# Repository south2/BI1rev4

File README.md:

BI1rev4
=======

BI1 revision 4 (myf14 evaluated, myf17 is work in progress)

The “body interactor”(BI) is a printed circuit board (PCB) with a vibrator motor, an accelerometer, a LiPo battery and battery charger and wireless radio frequency (RF) communication. The board can be programmed with the Arduino software.

The BI is designed for building a wearable autonomous device: With the accelerometer, movement data can be recorded and send to other BI by wireless RF communication. Gestures can be recognised and used for controlling the vibrator motor as well as other devices and applications using wireless communication (e.g. other BIs, computer games).

Different vibration pattern can be used to give the wearer information or feedback. Other use cases for vibration are massage application or moving objects (e.g. “vibrobot”).

The development board is particular suitable for people who are interested in application development using this kind of hardware arrangement and to construct an individual printed encasement for the board. Board, 3D printed encasement and Arduino program together are the individual final product. In addition the wireless communication function offers applications comprising multiple BI in different cases and with different tasks. In contrast changes, adaption or extensions (shields) of the board are rather complex.

www.bodyinteraction.com/about

Encasements

http://www.thingiverse.com/thing:109167

http://www.thingiverse.com/thing:259780

Data

- Atmel Attiny84 (8kbyte)
- LiPo charger (via USB)
- LiPo battery
- vibration motor (PWM controlled)
- BMA020 accelerometer
- two additional I/O ports  
- ISP interface (2×3 pole header) for programming
- RFM12B (915 or 868 Mhz)
- approx.  22×35 mm
- open source hardware

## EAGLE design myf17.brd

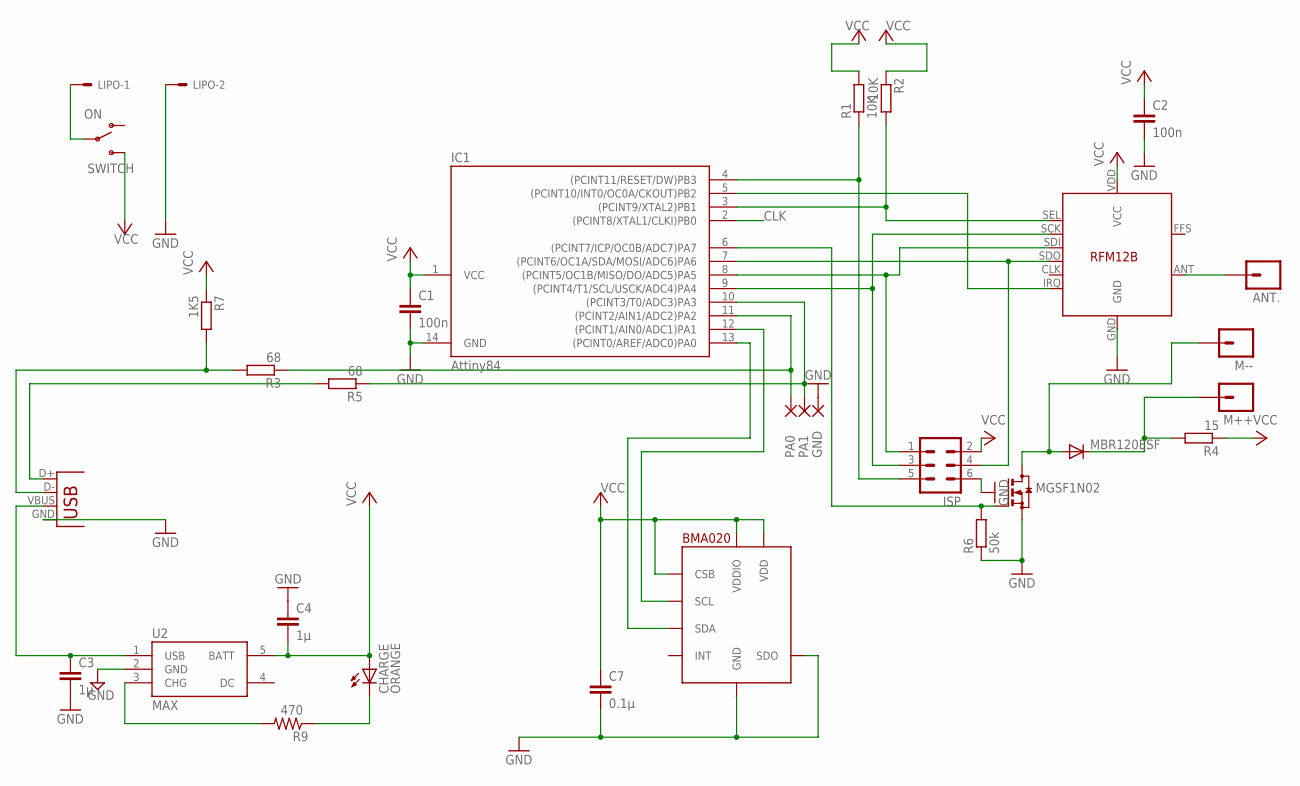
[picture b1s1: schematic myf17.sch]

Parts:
ANT.: M01PTH; 1X01
BMA020: BMA020; LBA-12
C1, C2: 100n; C0603K
C3, C4: 1µ; 0603-CAP
C7: 0.1µ; 0603-CAP
CHARGE: ORANGE; LED-0603
GND: SMD2; SMD1,27-2,54
IC1: Attiny84; SOIC14
ISP: MA03-2S; MA03-2-0.8
LIPO: SM02B-SRSS-TB
M++: M01PTH; 1X01
M--: M01PTH; 1X01
MBR120ESF: CGRM4001-G; SOD-123_MINI-SMA
MGSF1N02: BSS123; SOT23
PA0, PA1: SMD2; SMD1,27-2,54
R1, R2: 10K; R0603
R3, R5: 68; R0603
R4: 15; R0603
R6: 50k; R0603
R7: 1K5; R0603
R9: 470; R0603
RFM12B: RFM12B
SWITCH: ON; SWITCH-SPDT-SMD
U2: MAX; SOT23-5
USB: USB-MICROB

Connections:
CLK: IC1.2 ((PCINT8/XTAL1/CLKI)PB0)
GND: BMA020.P$3 (GND), BMA020.P$7 (SDO), C1.2, C2.2, C3.2, C4.1, C7.2, GND.1, IC1.14 (GND), ISP.6, LIPO.2, MGSF1N02.2 (S), R6.1, RFM12B.GND, U2.2 (GND), USB.GND
LED: BMA020.P$8 (SDA), IC1.13 ((PCINT0/AREF/ADC0)PA0)
unnamed: IC1.4 ((PCINT11/RESET/DW)PB3), ISP.5, R1.1
unnamed: IC1.3 ((PCINT9/XTAL2)PB1), R2.2, RFM12B.SEL
unnamed: ANT..1, RFM12B.ANT
unnamed: IC1.9 ((PCINT4/T1/SCL/USCK/ADC4)PA4), ISP.3, RFM12B.SCK
unnamed: IC1.8 ((PCINT5/OC1B/MISO/DO/ADC5)PA5), ISP.1, RFM12B.SDI
unnamed: IC1.7 ((PCINT6/OC1A/SDA/MOSI/ADC6)PA6), ISP.4, RFM12B.SDO
unnamed: IC1.5 ((PCINT10/INT0/OC0A/CKOUT)PB2), RFM12B.IRQ
unnamed: IC1.6 ((PCINT7/ICP/OC0B/ADC7)PA7), MGSF1N02.1 (G), R6.2
unnamed: IC1.10 ((PCINT3/T0/ADC3)PA3), PA1.1, R5.1
unnamed: IC1.11 ((PCINT2/AIN1/ADC2)PA2), PA0.1, R3.1
unnamed: BMA020.P$6 (SCL), IC1.12 ((PCINT1/AIN0/ADC1)PA1)
unnamed: M++.1, MBR120ESF.C, R4.2
unnamed: M--.1, MBR120ESF.A, MGSF1N02.3 (D)
unnamed: C3.1, U2.1 (USB), USB.VBUS
unnamed: LIPO.1, SWITCH.2
unnamed: R3.2, R7.2, USB.D-
unnamed: R5.2, USB.D+
unnamed: CHARGE.C, R9.1
unnamed: R9.2, U2.3 (CHG)
VCC: BMA020.P$2 (VDD), BMA020.P$5 (CSB), BMA020.P$9 (VDDIO), C1.1, C2.1, C4.2, C7.1, CHARGE.A, IC1.1 (VCC), ISP.2, R1.2, R2.1, R4.1, R7.1, RFM12B.VDD (VCC), SWITCH.3 (S), U2.5 (BATT)

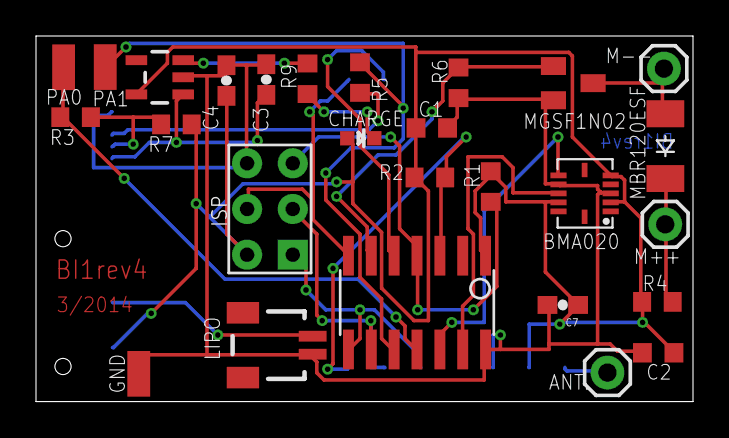
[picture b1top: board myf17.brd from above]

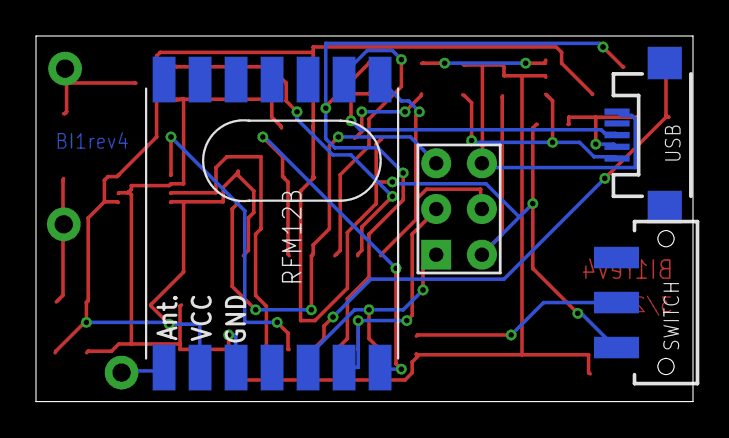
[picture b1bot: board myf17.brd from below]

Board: 4 copper layers, 36.5 x 20.3 mm, 30 parts (3 on the bottom side), 22 nets.

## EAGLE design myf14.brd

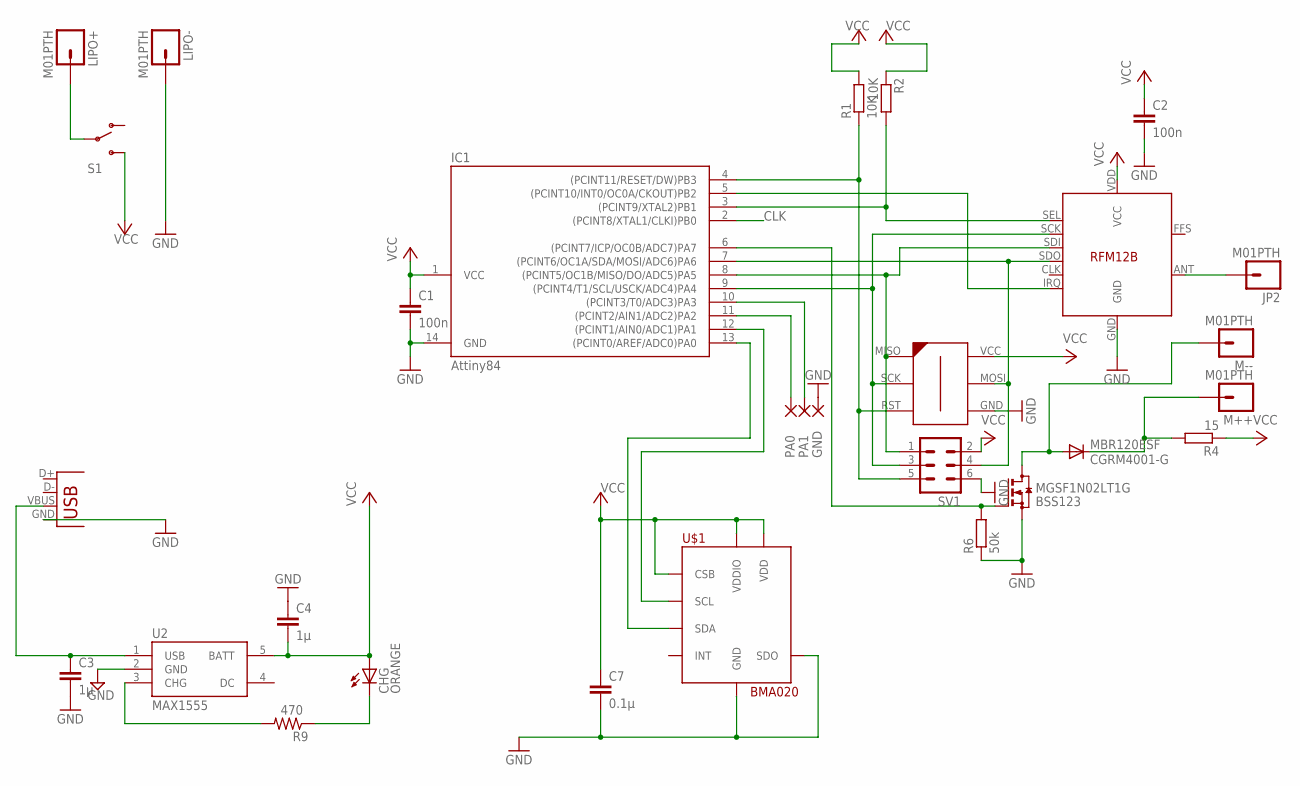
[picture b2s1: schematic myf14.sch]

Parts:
C1, C2: 100n; C0603K
C3, C4: 1µ; 0603-CAP
C7: 0.1µ; 0603-CAP
CHG: ORANGE; LED-0603
GND: SMD2; SMD1,27-2,54
IC1: Attiny84; SOIC14
JP2: M01PTH; 1X01
LIPO+: M01PTH; 1X01
LIPO-: M01PTH; 1X01
M++: M01PTH; 1X01
M--: M01PTH; 1X01
MBR120ESF: CGRM4001-G; SOD-123_MINI-SMA
MGSF1N02LT1G: BSS123; SOT23
PA0, PA1: SMD2; SMD1,27-2,54
R1, R2: 10K; R0603
R4: 15; R0603
R6: 50k; R0603
R9: 470; R0603
RFM12B: RFM12B
S1: SWITCH-SPDTSMD; AYZ0202
SV1: MA03-2S; MA03-2-0.8
U2: MAX1555; SOT23-5
U$1: BMA020; LBA-12
U$2: AVR-ISP-6-EDGE; 6PAD_ISP
X1: USB-MICROB

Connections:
CLK: IC1.2 ((PCINT8/XTAL1/CLKI)PB0)
GND: C1.2, C2.2, C3.2, C4.1, C7.2, GND.1, IC1.14 (GND), LIPO-.1, MGSF1N02LT1G.2 (S), R6.1, RFM12B.GND, SV1.6, U2.2 (GND), U$1.P$3 (GND), U$1.P$7 (SDO), U$2.GND, X1.GND
LED: IC1.13 ((PCINT0/AREF/ADC0)PA0), U$1.P$8 (SDA)
unnamed: IC1.4 ((PCINT11/RESET/DW)PB3), R1.1, SV1.5, U$2.RST
unnamed: IC1.3 ((PCINT9/XTAL2)PB1), R2.2, RFM12B.SEL
unnamed: JP2.1, RFM12B.ANT
unnamed: IC1.9 ((PCINT4/T1/SCL/USCK/ADC4)PA4), RFM12B.SCK, SV1.3, U$2.SCK
unnamed: IC1.8 ((PCINT5/OC1B/MISO/DO/ADC5)PA5), RFM12B.SDI, SV1.1, U$2.MISO
unnamed: IC1.7 ((PCINT6/OC1A/SDA/MOSI/ADC6)PA6), RFM12B.SDO, SV1.4, U$2.MOSI
unnamed: IC1.5 ((PCINT10/INT0/OC0A/CKOUT)PB2), RFM12B.IRQ
unnamed: IC1.6 ((PCINT7/ICP/OC0B/ADC7)PA7), MGSF1N02LT1G.1 (G), R6.2
unnamed: IC1.10 ((PCINT3/T0/ADC3)PA3), PA1.1
unnamed: IC1.11 ((PCINT2/AIN1/ADC2)PA2), PA0.1
unnamed: IC1.12 ((PCINT1/AIN0/ADC1)PA1), U$1.P$6 (SCL)
unnamed: M++.1, MBR120ESF.C, R4.2
unnamed: M--.1, MBR120ESF.A, MGSF1N02LT1G.3 (D)
unnamed: C3.1, U2.1 (USB), X1.VBUS
unnamed: LIPO+.1, S1.2
unnamed: CHG.C, R9.1
unnamed: R9.2, U2.3 (CHG)
VCC: C1.1, C2.1, C4.2, C7.1, CHG.A, IC1.1 (VCC), R1.2, R2.1, R4.1, RFM12B.VDD (VCC), S1.3 (S), SV1.2, U2.5 (BATT), U$1.P$2 (VDD), U$1.P$5 (CSB), U$1.P$9 (VDDIO), U$2.VCC

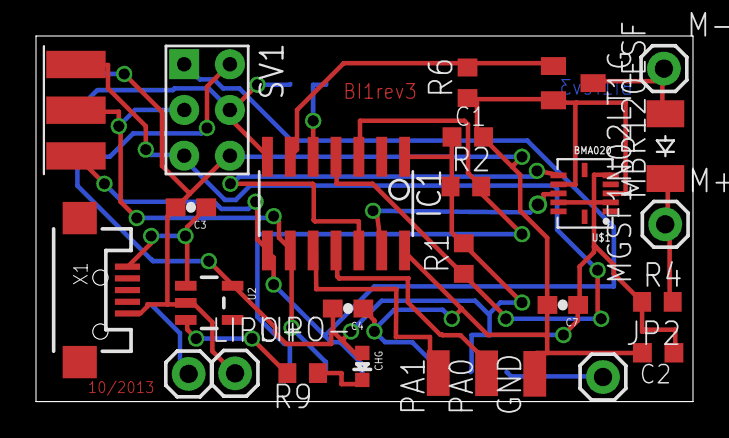
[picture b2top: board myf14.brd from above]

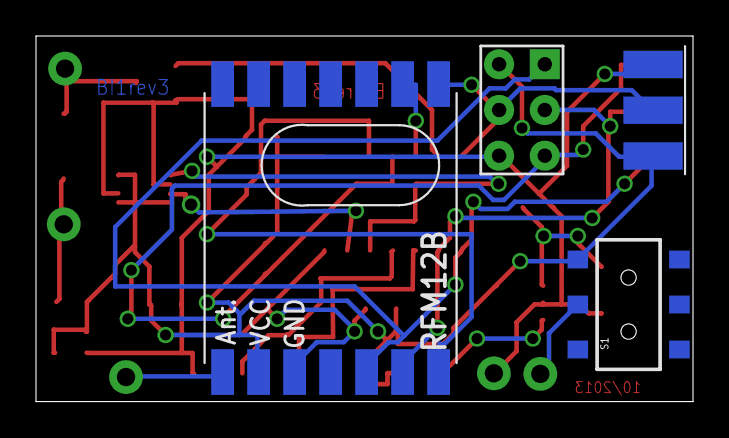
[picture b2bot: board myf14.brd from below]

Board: 4 copper layers, 36.5 x 20.3 mm, 29 parts (2 on the bottom side), 20 nets.

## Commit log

2014-03-25 BI1 circuit layout
2014-03-25 layout with V-USB

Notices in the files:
parts and their libraries:
SparkFun: Licensing: CC v3.0 Share-Alike You are welcome to use this library for commercial purposes.
